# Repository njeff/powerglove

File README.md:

# powerglove

Jeffrey Ni and Leon Wu

WIP haptic feedback distance sensing glove.

### PCB

### Hardware Design

### Integration

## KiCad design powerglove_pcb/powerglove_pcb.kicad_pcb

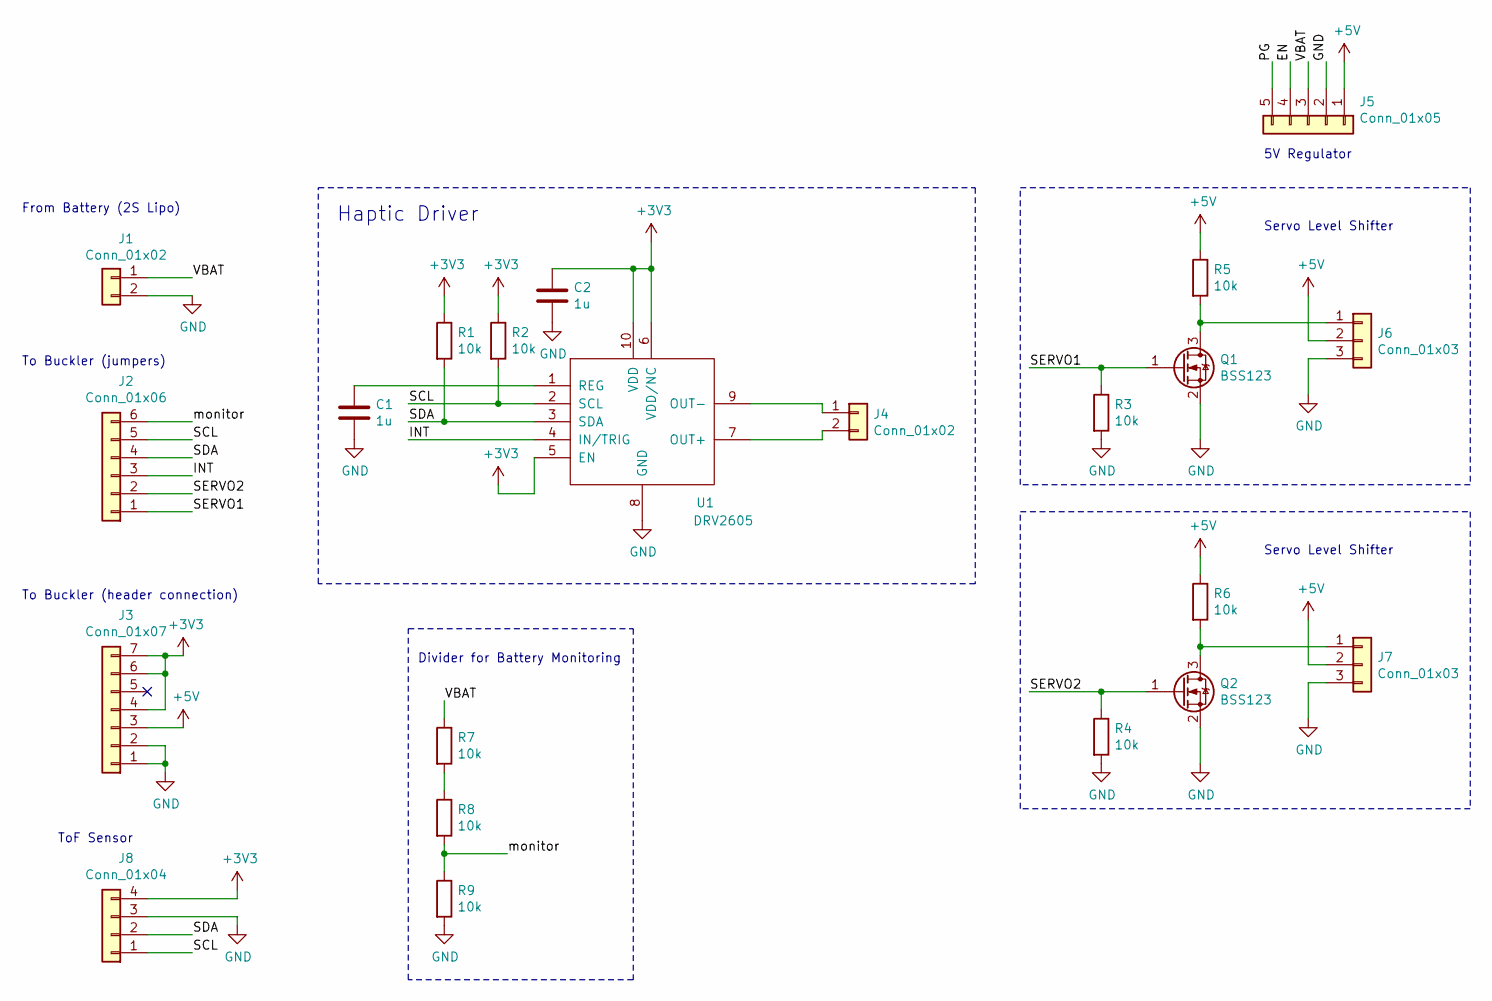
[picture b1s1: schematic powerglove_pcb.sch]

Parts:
C1, C2: 1u; C_0603_1608Metric_Pad1.05x0.95mm_HandSolder
J1: Conn_01x02; PinHeader_1x02_P2.54mm_Vertical
J2: Conn_01x06; PinHeader_1x06_P2.54mm_Vertical
J3: Conn_01x07; PinHeader_1x07_P2.54mm_Vertical
J4: Conn_01x02; PinHeader_2x01_P2.54mm_Vertical
J5: Conn_01x05; PinHeader_1x05_P2.54mm_Vertical
J6, J7: Conn_01x03; PinHeader_1x03_P2.54mm_Vertical
J8: Conn_01x04; PinHeader_1x04_P2.54mm_Vertical
Q1, Q2: BSS123; SOT-23
R1, R2, R3, R4, R5, R6, R7, R8, R9: 10k; R_0603_1608Metric_Pad1.05x0.95mm_HandSolder
U1: DRV2605; VSSOP-10_3x3mm_P0.5mm

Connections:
+3V3: C2.1, J3.4, J3.6, J3.7, J8.4, R1.1, R2.1, U1.5 (EN), U1.6 (VDD/NC), U1.10 (VDD)
+5V: J3.3, J5.1, J6.2, J7.2, R5.1, R6.1
/EN: J5.4
/INT: J2.3, U1.4 (IN/TRIG)
/PG: J5.5
/SCL: J2.5, J8.1, R2.2, U1.2 (SCL)
/SDA: J2.4, J8.2, R1.2, U1.3 (SDA)
/SERVO1: J2.1, Q1.1 (G), R3.1
/SERVO2: J2.2, Q2.1 (G), R4.1
/VBAT: J1.1, J5.3, R7.1
/monitor: J2.6, R8.2, R9.1
GND: C1.2, C2.2, J1.2, J3.1, J3.2, J5.2, J6.3, J7.3, J8.3, Q1.2 (S), Q2.2 (S), R3.2, R4.2, R9.2, U1.8 (GND)
unnamed: C1.1, U1.1 (REG)
unnamed: J4.1, U1.9 (OUT-)
unnamed: J4.2, U1.7 (OUT+)
unnamed: J6.1, Q1.3 (D), R5.2
unnamed: J7.1, Q2.3 (D), R6.2
unnamed: R7.2, R8.1

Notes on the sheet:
5V Regulator
Haptic Driver
Servo Level Shifter
To Buckler (header connection)
To Buckler (jumpers)
From Battery (2S Lipo)
ToF Sensor
Divider for Battery Monitoring

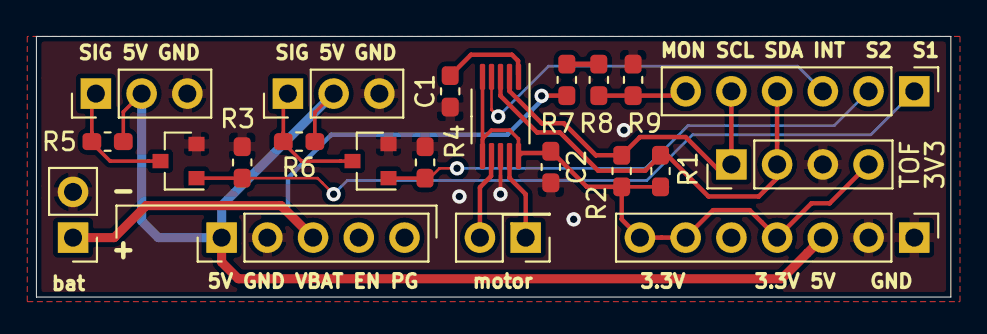
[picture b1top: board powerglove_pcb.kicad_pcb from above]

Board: 2 copper layers, 50.8 x 14.5 mm, 22 parts (0 on the bottom side), 16 nets.

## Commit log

2020-11-02 Preliminary architecture drawing
2020-11-02 Milestone 1 initial doc
2020-11-06 11/6 added ugly and still ambiguous sketches
2020-11-06 Updated architecture drawing
2020-11-09 Inital schematic
2020-11-09 updated schematic with assigned footprints, ported into layout
2020-11-09 some prelimiary layout placement b4 nap
2020-11-13 Added ToF sensor header, arrange layout
2020-11-13 PCB layout complete
2020-11-13 update PCB layout for simple battery monitoring, clean up silk
2020-11-13 PCB pictures, froge, and supplied driver for ToF sensor (not yet ported)
2020-11-13 update raytraced pcb images and adjusted PCB back zone
2020-11-13 better images with purple
2020-11-13 Generated gerbers
2020-11-15 Setup buckler toolchain
2020-11-15 Added haptic driver
2020-11-16 State machine setup
2020-11-17 exo_type1 sketch
2020-11-17 exob_ver sketch img
2020-11-20 VL53L0X Pololu Driver initial port, untested
2020-11-20 Milestone 2 doc
2020-11-23 Servo driver added, previous drivers tested
2020-11-26 Battery voltage reading
2020-11-30 Servo FB pin reading
2020-11-30 README update
2020-11-30 Debounced button
2020-12-01 Added simple calibration state
2020-12-08 Add auto-sleep state
2020-12-09 Added low power state, changed button reading to handle hold duration
2020-12-14 Run as fast as possible
2020-12-14 Battery voltage cutoff
2020-12-15 12/14 add related mechanical files
